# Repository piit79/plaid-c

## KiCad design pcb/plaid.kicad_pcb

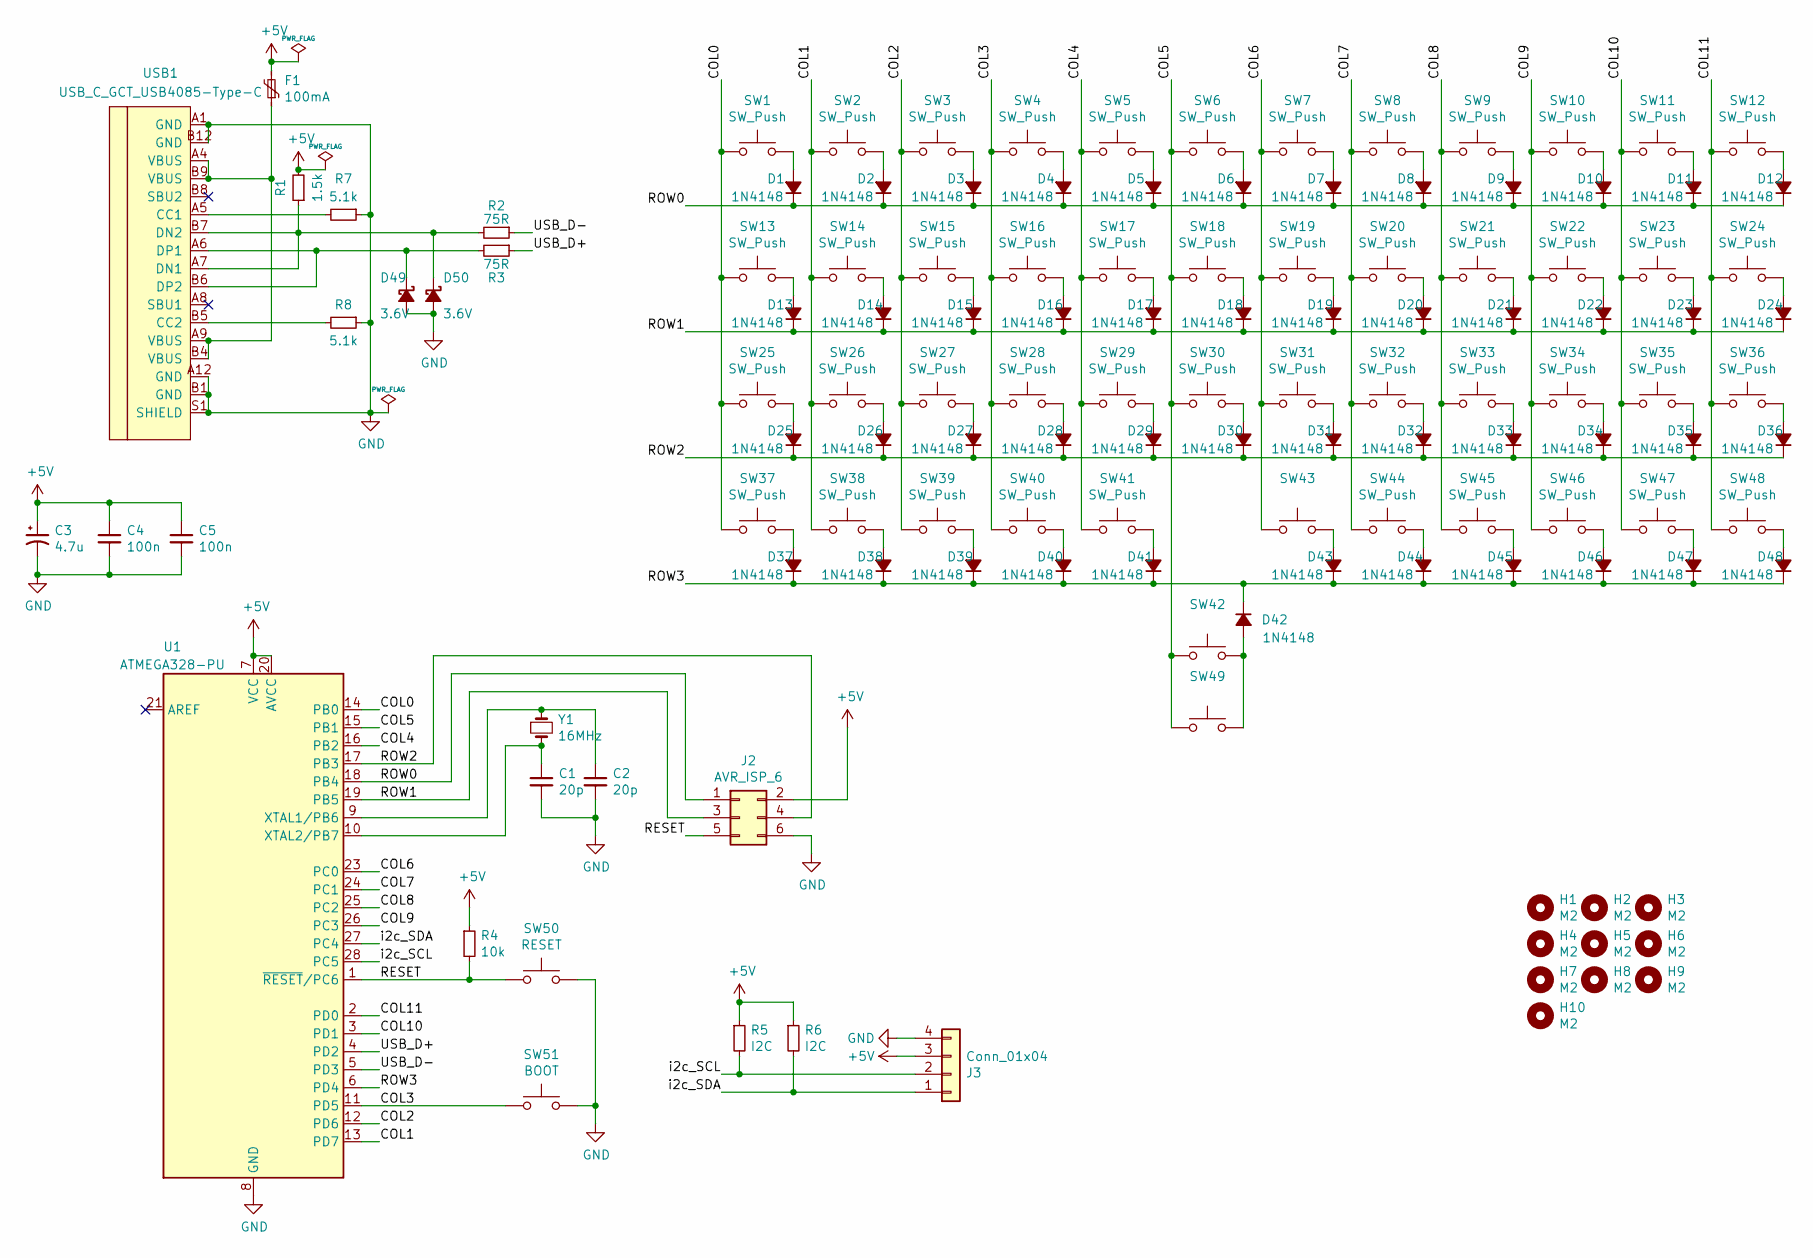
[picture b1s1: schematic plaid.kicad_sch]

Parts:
C1, C2: 20p; C_Disc_D3.0mm_W1.6mm_P2.50mm
C3: 4.7u; CP_Radial_D4.0mm_P1.50mm
C4, C5: 100n; C_Disc_D4.3mm_W1.9mm_P5.00mm
D1, D2, D3, D4, D5, D6, D7, D8, D9, D10, D11, D12, D13, D14, D15, D16, D17, D18, D19, D20, D21, D22, D23, D24, D25, D26, D27, D28, D29, D30, D31, D32, D33, D34, D35, D36, D37, D38, D39, D40, D41, D42, D43, D44, D45, D46, D47, D48: 1N4148; D_DO-35_SOD27_P5.08mm_Horizontal
D49, D50: 3.6V; D_DO-35_SOD27_P5.08mm_Horizontal
F1: 100mA; polyfuse_5.1mm
H1, H2, H3, H4, H5, H6, H7, H8, H9, H10: M2; MountingHole_2.2mm_M2_Pad
J2: AVR_ISP_6; Pin_Header_Straight_2x03_Pitch2.54mm
J3: Conn_01x04; OLED_v2
R1: 1.5k; R_Axial_DIN0204_L3.6mm_D1.6mm_P5.08mm_Horizontal
R2, R3: 75R; R_Axial_DIN0204_L3.6mm_D1.6mm_P5.08mm_Horizontal
R4: 10k; R_Axial_DIN0204_L3.6mm_D1.6mm_P5.08mm_Horizontal
R5, R6: I2C; R_Axial_DIN0204_L3.6mm_D1.6mm_P5.08mm_Horizontal
R7, R8: 5.1k; R_Axial_DIN0204_L3.6mm_D1.6mm_P5.08mm_Horizontal
SW1, SW2, SW3, SW4, SW5, SW6, SW7, SW8, SW9, SW10, SW11, SW12, SW13, SW14, SW15, SW16, SW17, SW18, SW19, SW20, SW21, SW22, SW23, SW24, SW25, SW26, SW27, SW28, SW29, SW30, SW31, SW32, SW33, SW34, SW35, SW36, SW37, SW38, SW39, SW40, SW41, SW44, SW45, SW46, SW47, SW48: SW_Push; MX-Choc-1U-NoLED
SW42, SW43, SW49: (no value)
SW50: RESET; SW_PUSH_6mm
SW51: BOOT; SW_PUSH_6mm
U1: ATMEGA328-PU; DIP-28_W7.62mm
USB1: USB_C_GCT_USB4085-Type-C; USB_C_GCT_USB4085-offset-pads
Y1: 16MHz; Crystal_HC49-4H_Vertical

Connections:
+5V: C3.1, C4.1, C5.1, F1.2, J2.2, J3.3, R1.2, R4.1, R5.1, R6.1, U1.7 (VCC), U1.20 (AVCC)
/COL0: SW1.2, SW13.2, SW25.2, SW37.2, U1.14 (PB0)
/COL1: SW2.2, SW14.2, SW26.2, SW38.2, U1.13 (PD7)
/COL2: SW3.2, SW15.2, SW27.2, SW39.2, U1.12 (PD6)
/COL3: SW4.2, SW16.2, SW28.2, SW40.2, SW51.1, U1.11 (PD5)
/COL4: SW5.2, SW17.2, SW29.2, SW41.2, U1.16 (PB2)
/COL5: SW6.2, SW18.2, SW30.2, SW42.2, SW49.2, U1.15 (PB1)
/COL6: SW7.2, SW19.2, SW31.2, SW43.2, U1.23 (PC0)
/COL7: SW8.2, SW20.2, SW32.2, SW44.2, U1.24 (PC1)
/COL8: SW9.2, SW21.2, SW33.2, SW45.2, U1.25 (PC2)
/COL9: SW10.2, SW22.2, SW34.2, SW46.2, U1.26 (PC3)
/COL10: SW11.2, SW23.2, SW35.2, SW47.2, U1.3 (PD1)
/COL11: SW12.2, SW24.2, SW36.2, SW48.2, U1.2 (PD0)
/RESET: J2.5, R4.2, SW50.1, U1.1 (~RESET/PC6)
/ROW0: D1.1 (K), D2.1 (K), D3.1 (K), D4.1 (K), D5.1 (K), D6.1 (K), D7.1 (K), D8.1 (K), D9.1 (K), D10.1 (K), D11.1 (K), D12.1 (K), J2.1, U1.18 (PB4)
/ROW1: D13.1 (K), D14.1 (K), D15.1 (K), D16.1 (K), D17.1 (K), D18.1 (K), D19.1 (K), D20.1 (K), D21.1 (K), D22.1 (K), D23.1 (K), D24.1 (K), J2.3, U1.19 (PB5)
/ROW2: D25.1 (K), D26.1 (K), D27.1 (K), D28.1 (K), D29.1 (K), D30.1 (K), D31.1 (K), D32.1 (K), D33.1 (K), D34.1 (K), D35.1 (K), D36.1 (K), J2.4, U1.17 (PB3)
/ROW3: D37.1 (K), D38.1 (K), D39.1 (K), D40.1 (K), D41.1 (K), D42.1 (K), D43.1 (K), D44.1 (K), D45.1 (K), D46.1 (K), D47.1 (K), D48.1 (K), U1.6 (PD4)
/USB_D+: R2.1, U1.4 (PD2)
/USB_D-: R3.1, U1.5 (PD3)
/i2c_SCL: J3.2, R5.2, U1.28 (PC5)
/i2c_SDA: J3.1, R6.2, U1.27 (PC4)
GND: C1.2, C2.2, C3.2, C4.2, C5.2, D49.2 (A), D50.2 (A), J2.6, J3.4, R7.1, R8.1, SW50.2, SW51.2, U1.8 (GND), U1.22 (GND), USB1.A1 (GND), USB1.A12 (GND), USB1.B1 (GND), USB1.B12 (GND), USB1.S1 (SHIELD)
unnamed: C1.1, U1.10 (XTAL2/PB7), Y1.2
unnamed: C2.1, U1.9 (XTAL1/PB6), Y1.1
unnamed: D1.2 (A), SW1.1
unnamed: D2.2 (A), SW2.1
unnamed: D3.2 (A), SW3.1
unnamed: D4.2 (A), SW4.1
unnamed: D5.2 (A), SW5.1
unnamed: D6.2 (A), SW6.1
unnamed: D7.2 (A), SW7.1
unnamed: D8.2 (A), SW8.1
unnamed: D9.2 (A), SW9.1
unnamed: D10.2 (A), SW10.1
unnamed: D11.2 (A), SW11.1
unnamed: D12.2 (A), SW12.1
unnamed: D13.2 (A), SW13.1
unnamed: D14.2 (A), SW14.1
unnamed: D15.2 (A), SW15.1
unnamed: D16.2 (A), SW16.1
unnamed: D17.2 (A), SW17.1
unnamed: D18.2 (A), SW18.1
unnamed: D19.2 (A), SW19.1
unnamed: D20.2 (A), SW20.1
unnamed: D21.2 (A), SW21.1
unnamed: D22.2 (A), SW22.1
unnamed: D23.2 (A), SW23.1
unnamed: D24.2 (A), SW24.1
unnamed: D25.2 (A), SW25.1
unnamed: D26.2 (A), SW26.1
unnamed: D27.2 (A), SW27.1
unnamed: D28.2 (A), SW28.1
unnamed: D29.2 (A), SW29.1
unnamed: D30.2 (A), SW30.1
unnamed: D31.2 (A), SW31.1
unnamed: D32.2 (A), SW32.1
unnamed: D33.2 (A), SW33.1
unnamed: D34.2 (A), SW34.1
unnamed: D35.2 (A), SW35.1
unnamed: D36.2 (A), SW36.1
unnamed: D37.2 (A), SW37.1
unnamed: D38.2 (A), SW38.1
unnamed: D39.2 (A), SW39.1
unnamed: D40.2 (A), SW40.1
unnamed: D41.2 (A), SW41.1
unnamed: D42.2 (A), SW42.1, SW49.1
unnamed: D43.2 (A), SW43.1
unnamed: D44.2 (A), SW44.1
unnamed: D45.2 (A), SW45.1
unnamed: D46.2 (A), SW46.1
unnamed: D47.2 (A), SW47.1
unnamed: D48.2 (A), SW48.1
unnamed: D49.1 (K), R2.2, USB1.A6 (DP1), USB1.B6 (DP2)
unnamed: D50.1 (K), R1.1, R3.2, USB1.A7 (DN1), USB1.B7 (DN2)
unnamed: F1.1, USB1.A4 (VBUS), USB1.A9 (VBUS), USB1.B4 (VBUS), USB1.B9 (VBUS)
unnamed: R7.2, USB1.A5 (CC1)
unnamed: R8.2, USB1.B5 (CC2)

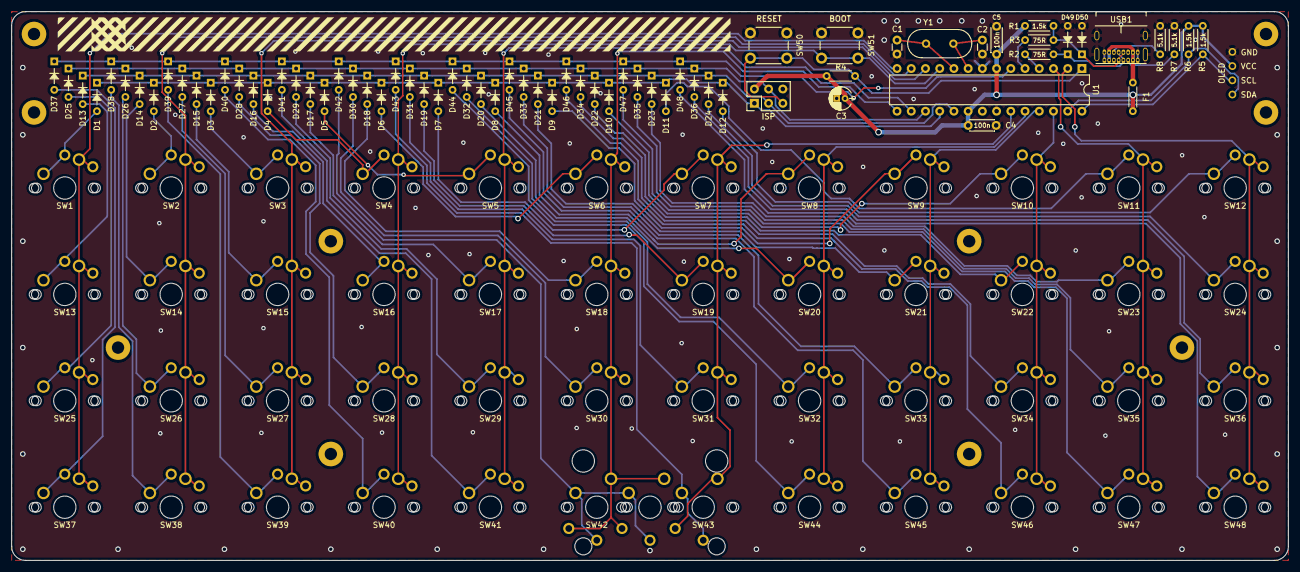
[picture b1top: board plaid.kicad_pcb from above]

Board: 2 copper layers, 228.0 x 98.0 mm, 130 parts (0 on the bottom side), 78 nets.

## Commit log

2021-01-15 Replace Mini USB connector with USB-C
2021-01-16 Add gerber zip files
2021-01-16 Add switch plate (MIT layout)
2021-01-16 Add plate gerber zip
2021-02-03 Add switch plate files (MIT and grid layouts)
2022-03-31 Move elyt away from OLED; use USB-C with offset pads; switch to KiCad 6 filenames
2022-03-31 Add KiCad library SMKJP_kicad_components as a submodule
2022-03-31 Add 42. Keebs KiCad library as a submodule
2022-03-31 Add support for Kailh Choc switches
2022-03-31 Remove library SMKJP_kicad_components/submodule
2022-03-31 Add universal MIT/grid plate
2022-04-05 Update the 42. Keebs library submodule
2022-04-06 Fix spacebar(s) - use "opposing" footprints
2022-04-06 Remove SMKJP_kicad_components library/submodule

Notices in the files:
pcb/plaid.kicad_pcb:
(c) 2019 Takuya Urakawa, Dm9Records.com
